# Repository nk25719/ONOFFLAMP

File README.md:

## Summary

HOMEWORK 2

This repository is the outcome of my practice in designing PCBs.  
Here, I document the various evolutionary stages of my project.
I am practicing schematic and PCB designing using KiCad.

This is a 3D view of the ON OFF lamp cicuit PCB board  

On the left side is the schematic wiring of the ON OFF lamp circuit, while on the right side is the copper routing on the PCB of the ON OFF lamp circuit.  

## Details

* I learned how to use the KICAD built-in symbol libraries. 
* I learned how to use the KiCad built-in footprint libraries.
* I learned how to use the Manage symbol libraries to add a global library.
* I learned how to use the Manage footprint libraries to add a global library.
* I learned how to annotate the schematic.
* I learned how to run ERC.
* I learned how to align the schematic to the grid.
* I learned how to use the bulk editor to add specific fields for the symbols. A cost field can be useful to make a budget for manufacturing.
* I learned how to draw and write on different layers, and how to enable and disable different layers.
* I learned how to use a connecter, how to wire the connector in a circuit.

## Other
* I learned the word courage return, which means "Enter".
* I learned that special characters in the mark down read me file behave in the same way they behave in HTML.
* I learned to be aware of spaces and image wrapping in the mark down read me file.
* I learned how to paste an image in the markdown read me, and here's an image.

Here is another 3D view image with the 3D models for the "through hole" type component toggled.

## Credits
I would like to express my gratitude to the developers and maintainers of several platforms. Firstly, GitHub, for its project management features, issues tracking, and project board, which have consistently proven useful during our usage. Additionally, I extend my thanks to KiCAD for providing the tools necessary for schematic capture and PCB design. I also appreciate the inventors and developers of the Arduino ecosystem, whose tools and hardware have had a profoundly positive impact on many individuals.

Furthermore, I am grateful for the Public Invention platform, which has facilitated communication and collaboration. Special recognition goes to my exceptional mentors, Mr. Forrest Lee Ereckson and Mr. Robert Reed. Their guidance has been invaluable in navigating these projects, fostering skill development, and providing ongoing support. Their mentorship has empowered me to apply my knowledge to projects that benefit public invention.

## License

* Firmware: Affero GPL 3.0
* CERN Open Hardware Licence Version 2 - Strongly Reciprocal

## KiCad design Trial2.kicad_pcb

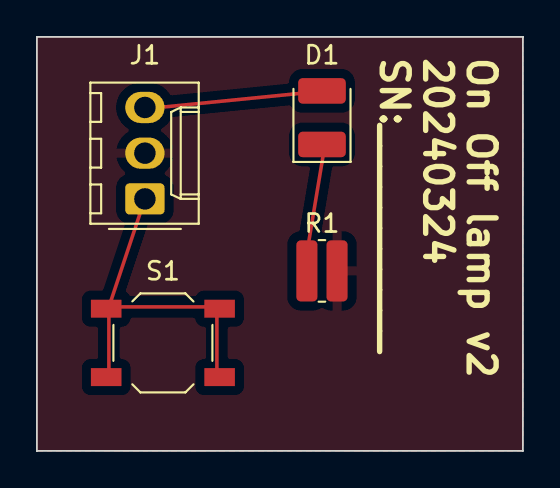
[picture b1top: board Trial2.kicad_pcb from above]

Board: 2 copper layers, 27.0 x 23.0 mm, 4 parts (0 on the bottom side), 4 nets, no tracks yet.

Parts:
D1: LED; LED_1210_3225Metric_Pad1.42x2.65mm_HandSolder
J1: Conn_01x03; Molex_KK-254_AE-6410-03A_1x03_P2.54mm_Vertical
R1: R_Small; R_0612_1632Metric_Pad1.18x3.40mm_HandSolder
S1: SWITCH_TACTILE_SPST-NO_0.05A_24V; SW_SPST_TL3342

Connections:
+3.3V: D1.2 (A), J1.3
GND: J1.2, R1.2
unnamed: D1.1 (K), R1.1
unnamed: J1.1, S1.1, S1.2

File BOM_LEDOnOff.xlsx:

Comment | Designator | Footprint
SWITCH_TACTILE_SPST-NO_0.05A_24V | S1 | SW_SPST_TL3342
LED | D1 | LED_1210_3225Metric_Pad1.42x2.65mm_HandSolder
Conn_01x03 | J1 | Molex_KK-254_AE-6410-03A_1x03_P2.54mm_Vertical
R_Small | R1 | R_0612_1632Metric_Pad1.18x3.40mm_HandSolder

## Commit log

2024-03-23 ONOFF LAMP CIRCUIT
    Initial commit
2024-03-24 Circuit Edits
    I added a Molex connector 01x03 and a Switch
    I added footprints for the connector and the Switch
    I added the sheet info
2024-03-26 Update README.md
    with the supervision of Mr. Erickson I added useful details about what I learned during this project
2024-03-26 Update README.md
    spell check
2024-03-27 Update README.md
    Spelling Correction
2024-04-06 Update README.md
    Improve description
2024-05-01 No further edits
    This project is on pause as is until further notice.
2024-06-02 Added gbr and pos files.
